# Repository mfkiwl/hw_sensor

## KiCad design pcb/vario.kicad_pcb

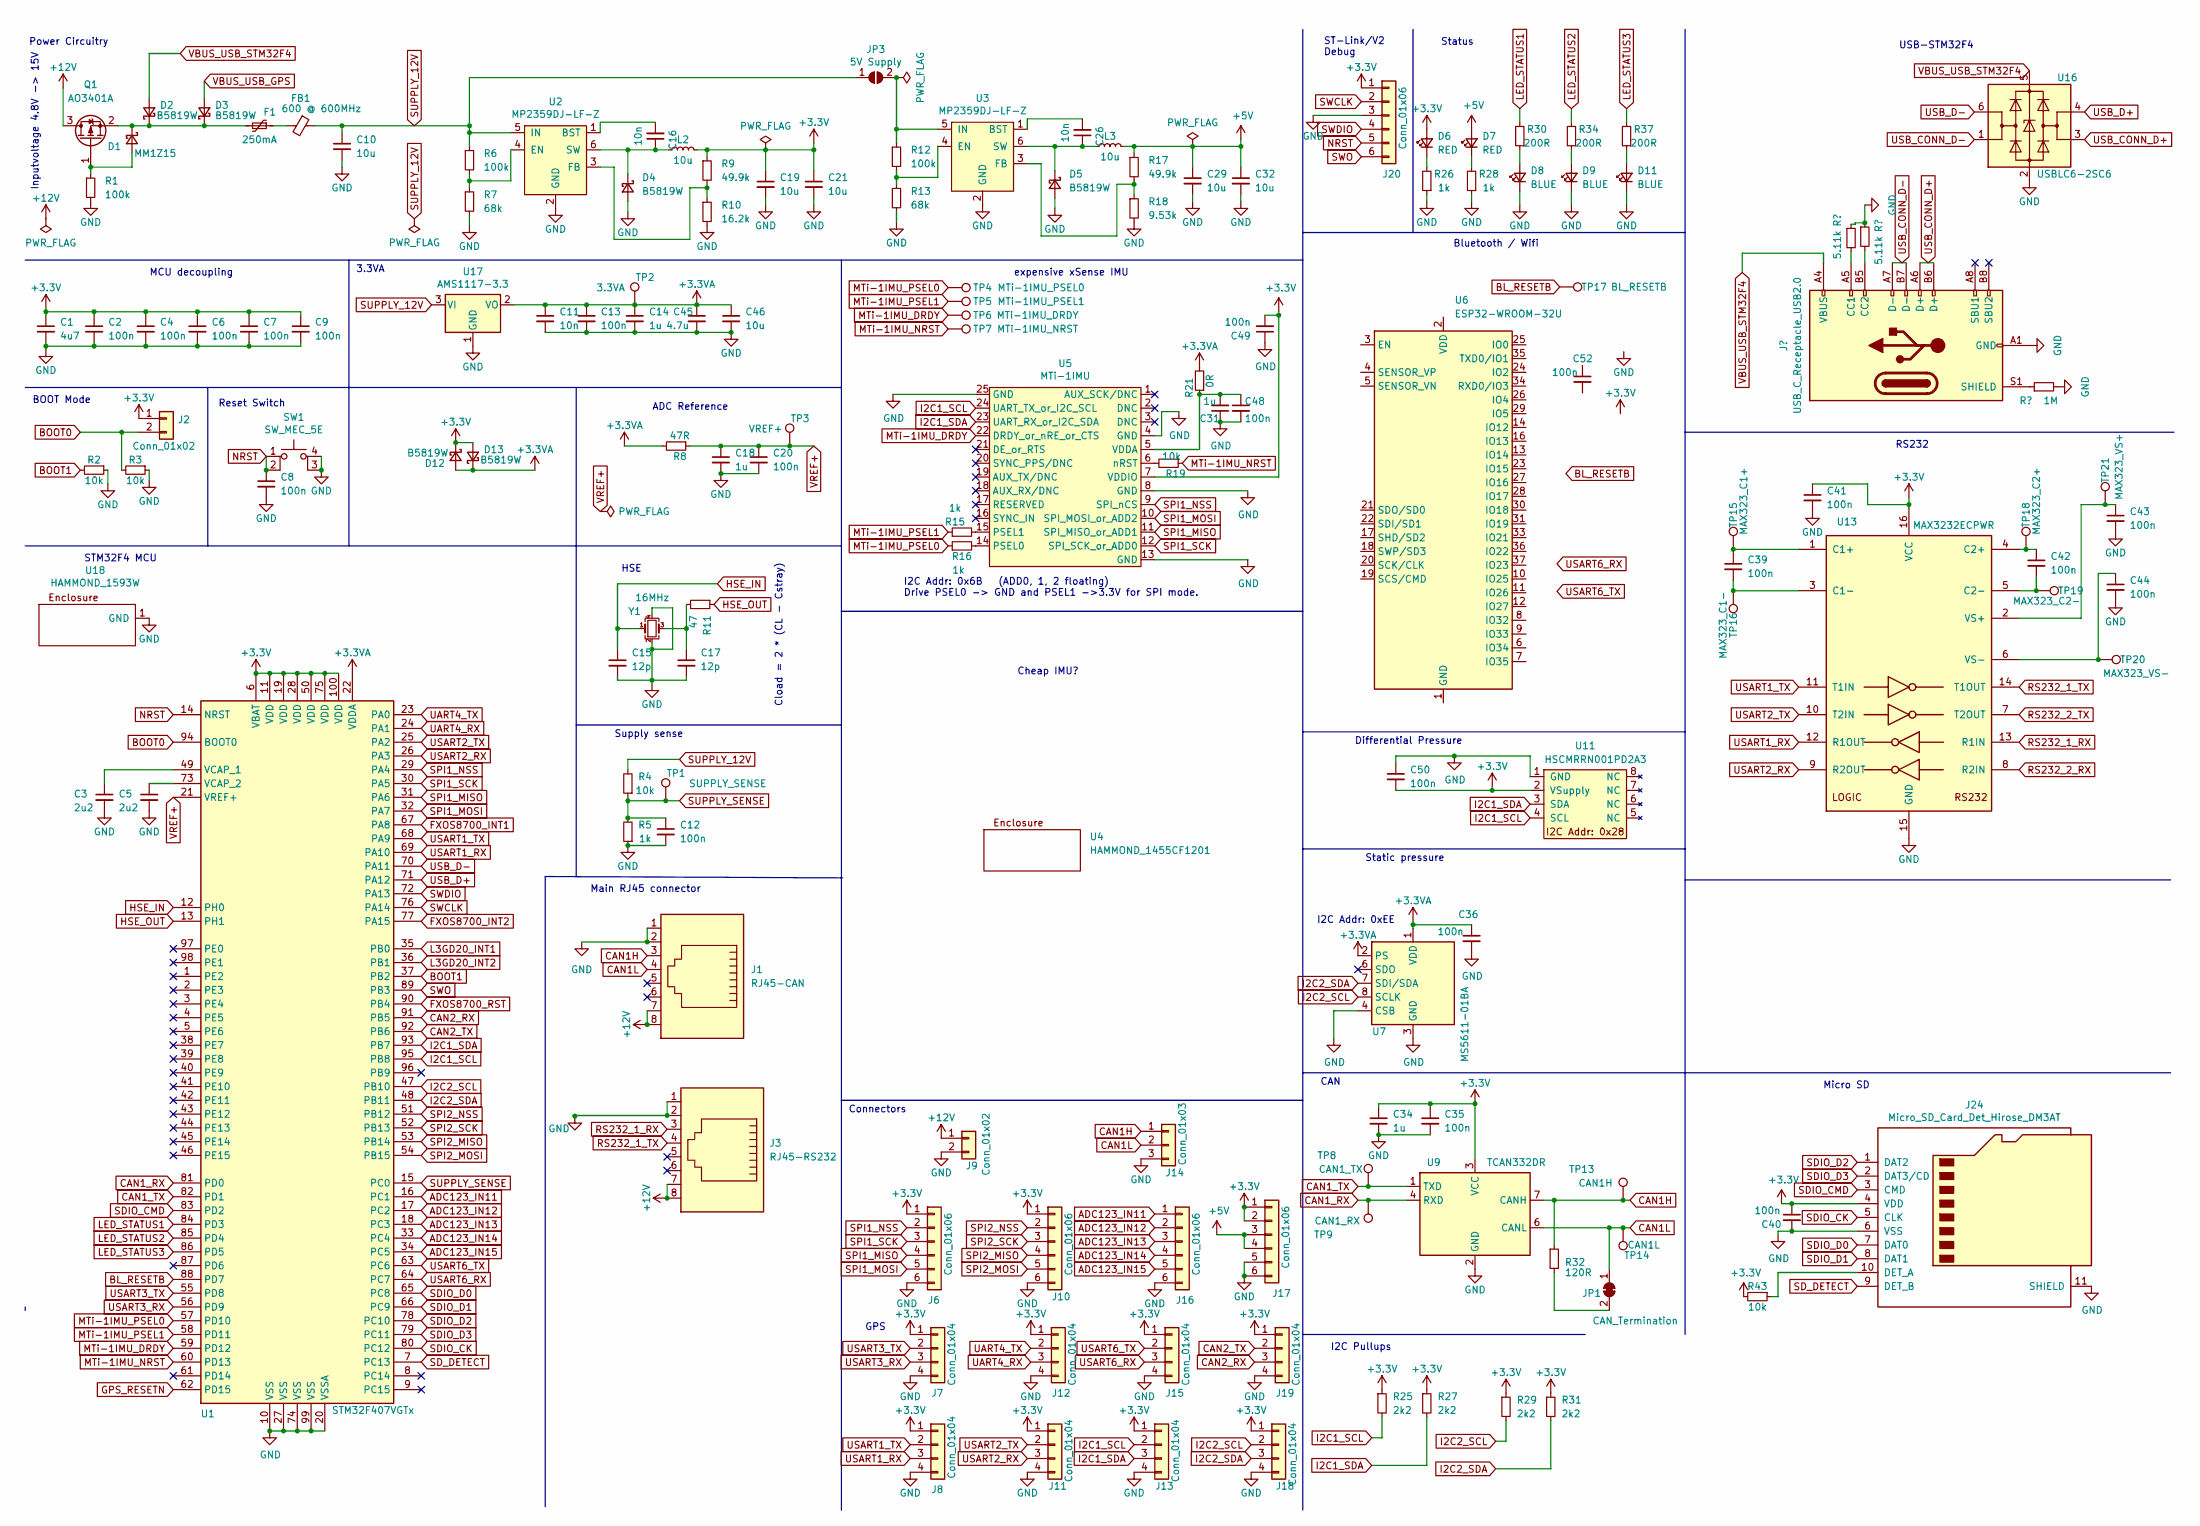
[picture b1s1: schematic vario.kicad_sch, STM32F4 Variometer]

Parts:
C1: 4u7; C_0603_1608Metric; LCSC Part # C19666
C2, C4, C6, C7, C8, C9, C12, C13, C20, C35, C36, C40, C41, C48, C49, C52: 100n; C_0402_1005Metric; LCSC Part # C1525
C3, C5: 2u2; C_0603_1608Metric; LCSC Part # C23630
C10, C19, C21, C29, C32, C46: 10u; C_1206_3216Metric; LCSC Part # C13585
C11: 10n; C_0402_1005Metric; LCSC Part # C15195
C14, C18, C31, C34: 1u; C_0402_1005Metric; LCSC Part # C52923
C15, C17: 12p; C_0402_1005Metric; LCSC Part # C1547
C16, C26: 10n; C_0603_1608Metric; LCSC Part # C57112
C39, C42, C43, C44, C50: 100n; C_0603_1608Metric; LCSC Part # C14663
C45: 4.7u; C_0805_2012Metric; LCSC Part # C1779
D1: MM1Z15; D_SOD-123; Mouser Part Number 785-SSCMRRN001PG2A3; LCSC Part # C86235
D2, D3, D4, D5, D12, D13: B5819W; D_SOD-123; LCSC Part # C8598
D6, D7: RED; LED_0603_1608Metric; LCSC Part # C2286
D8, D9, D11: BLUE; LED_0603_1608Metric; LCSC Part # C72041
F1: 250mA; Fuse_1206_3216Metric; LCSC Part # C369159
FB1: 600 @ 600MHz; L_0805_2012Metric; LCSC Part # C1017
J1: RJ45-CAN; RJ45_Amphenol_RJHSE5380
J2, J9: Conn_01x02; Molex_PicoBlade_53047-0210_1x02_P1.25mm_Vertical
J3: RJ45-RS232; RJ45_Amphenol_RJHSE5380
J6, J10, J16, J17, J20: Conn_01x06; Molex_PicoBlade_53048-0610_1x06_P1.25mm_Horizontal
J7, J8, J11, J12, J13, J15, J18, J19: Conn_01x04; Molex_PicoBlade_53048-0410_1x04_P1.25mm_Horizontal
J14: Conn_01x03; Molex_PicoBlade_53048-0310_1x03_P1.25mm_Horizontal
J24: Micro_SD_Card_Det_Hirose_DM3AT; microSD_HC_Hirose_DM3AT-SF-PEJM5; Mouser Part Number 798-DM3AT-SF-PEJM5; Mouser-Nr.: 798-DM3AT-SF-PEJM5
JP1: CAN_Termination; SolderJumper-2_P1.3mm_Bridged_Pad1.0x1.5mm
JP3: 5V Supply; SolderJumper-2_P1.3mm_Open_Pad1.0x1.5mm
L2, L3: 10u; L_Sunlord_MWSA0518_5.4x5.2mm; LCSC Part # C139506
Q1: AO3401A; SOT-23; LCSC Part # C15127
R1, R6, R12: 100k; R_0603_1608Metric; LCSC Part # C25803
R2, R3, R43: 10k; R_0402_1005Metric; LCSC Part # C25744
R4: 10k; R_1206_3216Metric; LCSC Part # C17902
R5, R15, R16, R26, R28: 1k; R_0603_1608Metric; LCSC Part # C21190
R7, R13: 68k; R_0603_1608Metric; LCSC Part # C23231
R8: 47R; R_0603_1608Metric; LCSC Part # C23182
R9, R17: 49.9k; R_0603_1608Metric; LCSC Part # C23184
R10: 16.2k; R_0603_1608Metric; LCSC Part # C22885
R11: 47; R_0402_1005Metric; LCSC Part # C25118
R18: 9.53k; R_0603_1608Metric; LCSC Part # C23127
R19: 10k; R_0603_1608Metric; LCSC Part # C25804
R21: 0R; R_0603_1608Metric; LCSC Part # C21189
R25, R27, R29, R31: 2k2; R_0402_1005Metric; LCSC Part # C25879
R30, R34, R37: 200R; R_0603_1608Metric; LCSC Part # C8218
R32: 120R; R_0603_1608Metric; LCSC Part # C22787
SW1: SW_MEC_5E; TS-1187A-C-E-B; LCSC C318889
TP1: SUPPLY_SENSE; TestPoint_Pad_1.5x1.5mm
TP2: 3.3VA; TestPoint_Pad_1.5x1.5mm
TP3: VREF+; TestPoint_Pad_1.5x1.5mm
TP4: MTi-1IMU_PSEL0; TestPoint_Pad_1.5x1.5mm
TP5: MTi-1IMU_PSEL1; TestPoint_Pad_1.5x1.5mm
TP6: MTi-1IMU_DRDY; TestPoint_Pad_1.5x1.5mm
TP7: MTi-1IMU_NRST; TestPoint_Pad_1.5x1.5mm
TP8: CAN1_TX; TestPoint_Pad_1.5x1.5mm
TP9: CAN1_RX; TestPoint_Pad_1.5x1.5mm
TP13: CAN1H; TestPoint_Pad_1.5x1.5mm
TP14: CAN1L; TestPoint_Pad_1.5x1.5mm
TP15: MAX323_C1+; TestPoint_Pad_1.5x1.5mm
TP16: MAX323_C1-; TestPoint_Pad_1.5x1.5mm
TP17: BL_RESETB; TestPoint_Pad_1.5x1.5mm
TP18: MAX323_C2+; TestPoint_Pad_1.5x1.5mm
TP19: MAX323_C2-; TestPoint_Pad_1.5x1.5mm
TP20: MAX323_VS-; TestPoint_Pad_1.5x1.5mm
TP21: MAX323_VS+; TestPoint_Pad_1.5x1.5mm
U1: STM32F407VGTx; LQFP-100_14x14mm_P0.5mm; LCSC Part # C12345
U2, U3: MP2359DJ-LF-Z; SOT-23-6; LCSC Part # C14259
U4: HAMMOND_1455CF1201
U5: MTi-1IMU; XSens_MTi1_IMU
U6: ESP32-WROOM-32U
U7: MS5611-01BA; LGA-8_3x5mm_P1.25mm; Mouser Part Number 824-MS561101BA03-50; Mouser-Nr.: 824-MS561101BA03-50
U9: TCAN332DR; SOIC-8_3.9x4.9mm_P1.27mm; LCSC Part # C73651
U11: HSCMRRN001PD2A3; SSCMRRN001PG2A3_SMT-8; Mouser-Nr.: 785-HSCMRRN001PD2A3
U13: MAX3232ECPWR; HTSSOP-16-1EP_4.4x5mm_P0.65mm_EP3x3mm; LCSC Part # C11317
U16: USBLC6-2SC6; SOT-23-6; LCSC Part # C7519
U17: AMS1117-3.3; SOT-223-3_TabPin2; LCSC C6186
U18: HAMMOND_1593W; HAMMOND_1593W_edge_cut_notallmountingholes; Mouser Part Number 546-1593WTBU, 546-1593WBK
Y1: 16MHz; Crystal_SMD_3225-4Pin_3.2x2.5mm; LCSC Part # C13738

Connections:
+3.3VA: C11.1, C13.1, C14.1, C36.1, C45.1, C46.1, D12.2 (A), D13.1 (K), R8.2, R21.2, TP2.1, U1.22 (VDDA), U7.1 (VDD), U7.2 (PS), U17.2 (VO)
+3V3: C1.1, C2.1, C4.1, C6.1, C7.1, C9.1, C19.1, C21.1, C34.1, C35.1, C40.1, C41.1, C49.2, C50.2, D6.2 (A), D12.1 (K), D13.2 (A), J2.1, J6.1, J7.1, J8.1, J10.1, J11.1, J12.1, J13.1, J15.1, J17.1, J17.2, J18.1, J19.1, J20.1, J24.4 (VDD), L2.2, R9.1, R25.1, R27.1, R29.1, R31.1, R43.2, U1.6 (VBAT), U1.11 (VDD), U1.19 (VDD), U1.28 (VDD), U1.50 (VDD), U1.75 (VDD), U1.100 (VDD), U5.7 (VDDIO), U9.3 (VCC), U11.2 (VSupply), U13.16 (VCC)
+5V: C29.1, C32.1, D7.2 (A), J17.3, J17.4, L3.2, R17.1
+12V: J1.7, J1.8, J3.7, J3.8, J9.1, Q1.3 (D)
ADC123_IN11: J16.1, U1.16 (PC1)
ADC123_IN12: J16.2, U1.17 (PC2)
ADC123_IN13: J16.3, U1.18 (PC3)
ADC123_IN14: J16.4, U1.33 (PC4)
ADC123_IN15: J16.5, U1.34 (PC5)
BL_RESETB: TP17.1, U1.88 (PD7)
BOOT0: J2.2, R3.2, U1.94 (BOOT0)
BOOT1: R2.2, U1.37 (PB2)
CAN1H: J1.3, J14.1, R32.1, TP13.1, U9.7 (CANH)
CAN1L: J1.4, J14.2, JP1.1 (A), TP14.1, U9.6 (CANL)
CAN1_RX: TP9.1, U1.81 (PD0), U9.4 (RXD)
CAN1_TX: TP8.1, U1.82 (PD1), U9.1 (TXD)
CAN2_RX: J19.3, U1.91 (PB5)
CAN2_TX: J19.2, U1.92 (PB6)
FXOS8700_INT1: U1.67 (PA8)
FXOS8700_INT2: U1.77 (PA15)
FXOS8700_RST: U1.90 (PB4)
GND: C1.2, C2.2, C3.2, C4.2, C5.2, C6.2, C7.2, C8.2, C9.2, C10.2, C11.2, C12.2, C13.2, C14.2, C15.2, C17.2, C18.2, C19.2, C20.2, C21.2, C29.2, C31.1, C32.2, C34.2, C35.2, C36.2, C40.2, C41.2, C43.2, C44.2, C45.2, C46.2, C48.2, C49.1, C50.1, D4.2 (A), D5.2 (A), D8.1 (K), D9.1 (K), D11.1 (K), J1.1, J1.2, J3.1, J3.2, J6.6, J7.4, J8.4, J9.2, J10.6, J11.4, J12.4, J13.4, J14.3, J15.4, J16.6, J17.5, J17.6, J18.4, J19.4, J20.3, J24.6 (VSS), J24.11 (SHIELD), R1.2, R2.1, R3.1, R5.1, R7.2, R10.2, R13.2, R18.2, R26.1, R28.1, SW1.3 (K), SW1.4 (A), U1.10 (VSS), U1.20 (VSSA), U1.27 (VSS), U1.74 (VSS), U1.99 (VSS), U2.2 (GND), U3.2 (GND), U5.4 (GND), U5.8 (GND), U5.13 (GND), U5.25 (GND), U7.3 (GND), U7.4 (CSB), U7.5 (CSB), U9.2 (GND), U11.1 (GND), U13.15 (GND), U16.2 (GND), U17.1 (GND), U18.1 (GND), Y1.2, Y1.4; also elsewhere on the board
GPS_RESETN: U1.62 (PD15)
HSE_IN: C15.1, U1.12 (PH0), Y1.1
HSE_OUT: R11.1, U1.13 (PH1)
I2C1_SCL: J13.2, R25.2, U1.95 (PB8), U5.24 (UART_TX_or_I2C_SCL), U11.4 (SCL)
I2C1_SDA: J13.3, R27.2, U1.93 (PB7), U5.23 (UART_RX_or_I2C_SDA), U11.3 (SDA)
I2C2_SCL: J18.2, R29.2, U1.47 (PB10), U7.8 (SCLK)
I2C2_SDA: J18.3, R31.2, U1.48 (PB11), U7.7 (SDI/SDA)
L3GD20_INT1: U1.35 (PB0)
L3GD20_INT2: U1.36 (PB1)
LED_STATUS1: R30.2, U1.84 (PD3)
LED_STATUS2: R34.2, U1.85 (PD4)
LED_STATUS3: R37.2, U1.86 (PD5)
MTi-1IMU_DRDY: TP6.1, U1.59 (PD12), U5.22 (DRDY_or_nRE_or_CTS)
MTi-1IMU_NRST: R19.1, TP7.1, U1.60 (PD13)
MTi-1IMU_PSEL0: R16.1, TP4.1, U1.57 (PD10)
MTi-1IMU_PSEL1: R15.1, TP5.1, U1.58 (PD11)
NRST: C8.1, J20.5, SW1.1, SW1.2, U1.14 (NRST)
unnamed: C3.1, U1.49 (VCAP_1)
unnamed: C5.1, U1.73 (VCAP_2)
unnamed: C16.1, D4.1 (K), L2.1, U2.6 (SW)
unnamed: C16.2, U2.1 (BST)
unnamed: C17.1, R11.2, Y1.3
unnamed: C26.1, D5.1 (K), L3.1, U3.6 (SW)
unnamed: C26.2, U3.1 (BST)
unnamed: C31.2, C48.1, R21.1, U5.5 (VDDA)
unnamed: C39.1, TP15.1, U13.1 (C1+)
unnamed: C39.2, TP16.1, U13.3 (C1-)
unnamed: C42.1, TP18.1, U13.4 (C2+)
unnamed: C42.2, TP19.1, U13.5 (C2-)
unnamed: C43.1, TP21.1, U13.2 (VS+)
unnamed: C44.1, TP20.1, U13.6 (VS-)
unnamed: D1.1 (K), D2.1 (K), D3.1 (K), F1.2, Q1.2 (S)
unnamed: D1.2 (A), Q1.1 (G), R1.1
unnamed: D6.1 (K), R26.2
unnamed: D7.1 (K), R28.2
unnamed: D8.2 (A), R30.1
unnamed: D9.2 (A), R34.1
unnamed: D11.2 (A), R37.1
unnamed: F1.1, FB1.2
unnamed: J24.10 (DET_A), R43.1
unnamed: JP1.2 (B), R32.2
unnamed: JP3.2 (B), R12.1, U3.5 (IN)
unnamed: R6.2, R7.1, U2.4 (EN)
unnamed: R9.2, R10.1, U2.3 (FB)
unnamed: R12.2, R13.1, U3.4 (EN)
unnamed: R15.2, U5.15 (PSEL1)
unnamed: R16.2, U5.14 (PSEL0)
unnamed: R17.2, R18.1, U3.3 (FB)
unnamed: R19.2, U5.6 (nRST)
unnamed: U6.1 (GND), U6.15 (GND), U6.38 (GND), U6.39 (GND)
RS232_1_RX: J3.3, U13.13 (R1IN)
RS232_1_TX: J3.4, U13.14 (T1OUT)
RS232_2_RX: U13.8 (R2IN)
RS232_2_TX: U13.7 (T2OUT)
SDIO_CK: J24.5 (CLK), U1.80 (PC12)
SDIO_CMD: J24.3 (CMD), U1.83 (PD2)
SDIO_D0: J24.7 (DAT0), U1.65 (PC8)
SDIO_D1: J24.8 (DAT1), U1.66 (PC9)
SDIO_D2: J24.1 (DAT2), U1.78 (PC10)
SDIO_D3: J24.2 (DAT3/CD), U1.79 (PC11)
SD_DETECT: J24.9 (DET_B), U1.7 (PC13)
SPI1_MISO: J6.4, U1.31 (PA6), U5.11 (SPI_MISO_or_ADD1)
SPI1_MOSI: J6.5, U1.32 (PA7), U5.10 (SPI_MOSI_or_ADD2)
SPI1_NSS: J6.2, U1.29 (PA4), U5.9 (SPI_nCS)
SPI1_SCK: J6.3, U1.30 (PA5), U5.12 (SPI_SCK_or_ADD0)
SPI2_MISO: J10.4, U1.53 (PB14)
SPI2_MOSI: J10.5, U1.54 (PB15)
SPI2_NSS: J10.2, U1.51 (PB12)
SPI2_SCK: J10.3, U1.52 (PB13)
SUPPLY_12V: C10.1, FB1.1, JP3.1 (A), R4.2, R6.1, U2.5 (IN), U17.3 (VI)
SUPPLY_SENSE: C12.1, R4.1, R5.2, TP1.1, U1.15 (PC0)
SWCLK: J20.2, U1.76 (PA14)
SWDIO: J20.4, U1.72 (PA13)
SWO: J20.6, U1.89 (PB3)
UART4_RX: J12.3, U1.24 (PA1)
UART4_TX: J12.2, U1.23 (PA0)
USART1_RX: J8.3, U1.69 (PA10), U13.12 (R1OUT)
USART1_TX: J8.2, U1.68 (PA9), U13.11 (T1IN)
USART2_RX: J11.3, U1.26 (PA3), U13.9 (R2OUT)
USART2_TX: J11.2, U1.25 (PA2), U13.10 (T2IN)
USART3_RX: J7.3, U1.56 (PD9)
USART3_TX: J7.2, U1.55 (PD8)
USART6_RX: J15.3, U1.64 (PC7)
USART6_TX: J15.2, U1.63 (PC6)
USB_CONN_D+: U16.3 (I/O2); also elsewhere on the board
USB_CONN_D-: U16.1 (I/O1); also elsewhere on the board
USB_D+: U1.71 (PA12), U16.4 (I/O2)
USB_D-: U1.70 (PA11), U16.6 (I/O1)
VBUS_USB_GPS: D3.2 (A)
VBUS_USB_STM32F4: D2.2 (A), U16.5 (VBUS); also elsewhere on the board
VREF+: C18.1, C20.1, R8.1, TP3.1, U1.21 (VREF+)

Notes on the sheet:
MCU decoupling
Micro SD
3.3VA
I2C Addr: 0x6B (ADD0, 1, 2 floating) Drive PSEL0 -> GND and PSEL1 ->3.3V for SPI mode.
RS232
Reset Switch
I2C Pullups
Static pressure
I2C Addr: 0xEE
CAN
Differential Pressure
ST-Link/V2 Debug
Inputvoltage 4.8V -> 15V
Cheap IMU?
USB-STM32F4
expensive xSense IMU
HSE
GPS
ADC Reference
Main RJ45 connector
Connectors
Supply sense
Bluetooth / Wifi
Power Circuitry
STM32F4 MCU
Status
Cload = 2 * (CL - Cstray)
BOOT Mode

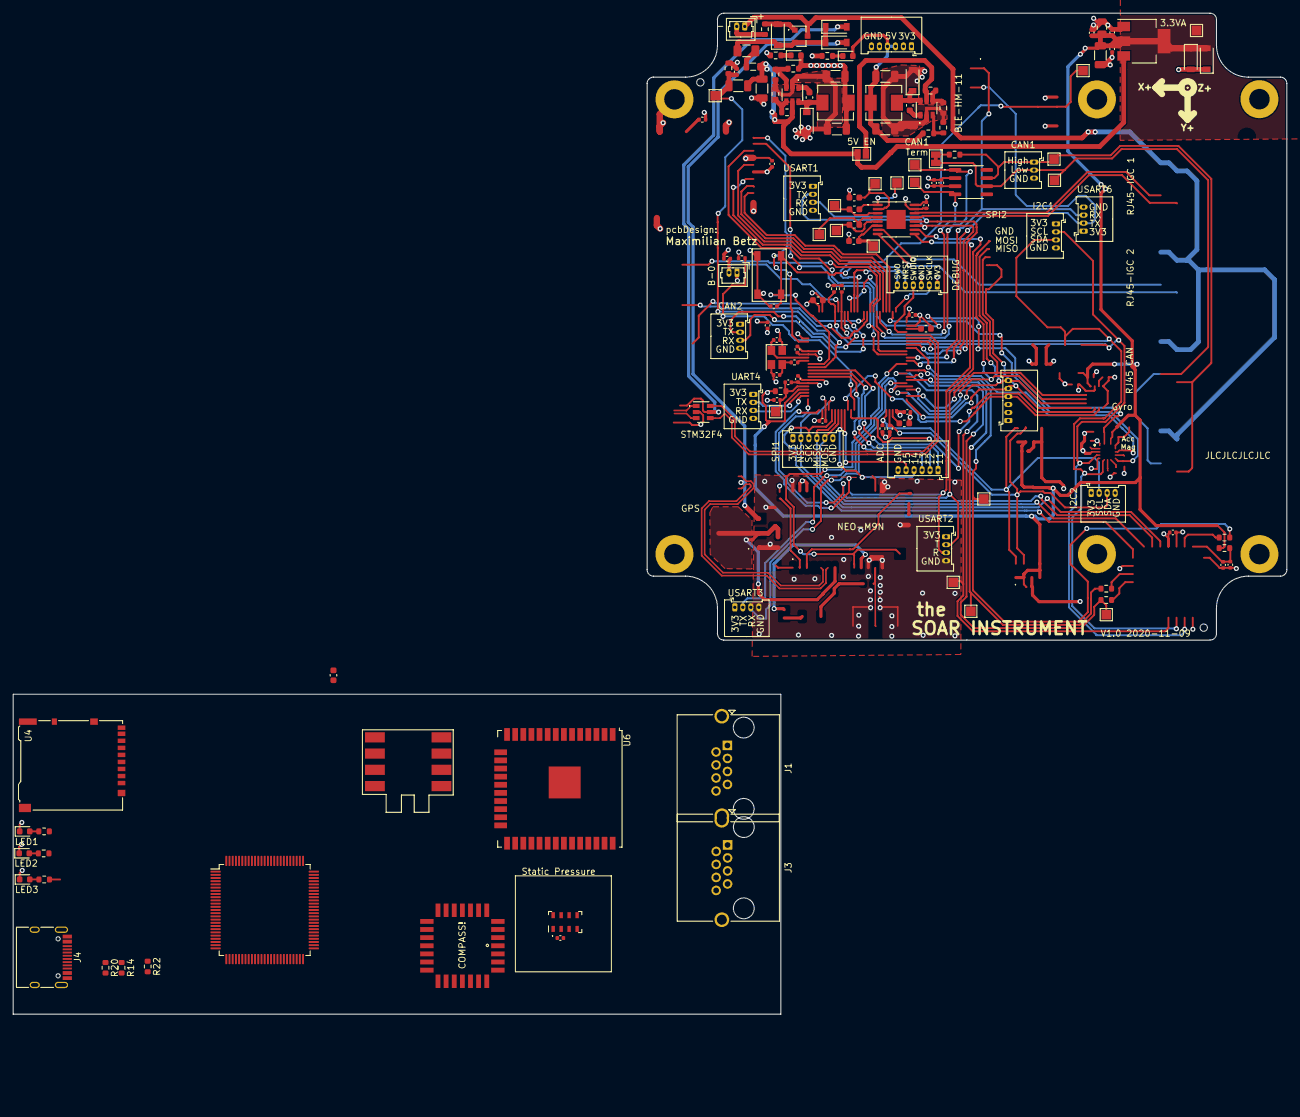
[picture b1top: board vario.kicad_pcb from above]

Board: 4 copper layers, 100.0 x 98.0 mm, 145 parts (0 on the bottom side), 107 nets.

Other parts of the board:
J4: USB_C_Receptacle_USB2.0; USB_C_Receptacle_HRO_TYPE-C-31-M-12
R14, R20: 5.11k; R_0603_1608Metric
R22: 1M; R_0603_1608Metric

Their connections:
GND: J4.A1 (GND), J4.A12 (GND), J4.B1 (GND), J4.B12 (GND), R14.1, R20.1, R22.2; also elsewhere on the board
unnamed: J4.A5 (CC1), R14.2
unnamed: J4.B5 (CC2), R20.2
unnamed: J4.S1 (SHIELD), R22.1
USB_CONN_D+: J4.A6 (D+), J4.B6 (D+); also elsewhere on the board
USB_CONN_D-: J4.A7 (D-), J4.B7 (D-); also elsewhere on the board
VBUS_USB_STM32F4: J4.A4 (VBUS), J4.A9 (VBUS), J4.B4 (VBUS), J4.B9 (VBUS); also elsewhere on the board

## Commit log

2022-04-08 started enclosure study for next version
